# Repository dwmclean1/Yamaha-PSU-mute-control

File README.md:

# Yamaha-PSU-mute-control

## What is it?

<p>Allows the use of non-original power supplies in older Yamaha rackmount audio devices.</p><br>

<br>

<p/>The board consists of the bridge rectifier, 3 100K resistor and phototransistor shown above. When the unit is powered on this circuit provides current to the mute control ciruit on the main board which will activate the mute relays after a short delay in order to avoid any loud spikes from the audio outputs.</p><br>

<br>

<p>Most Yamaha audio gear from this era used the same power supply board, or at least the same circuit, and if you want to replace the power supply with a newer version you may need this circuit. Use at your own risk.</p><br>

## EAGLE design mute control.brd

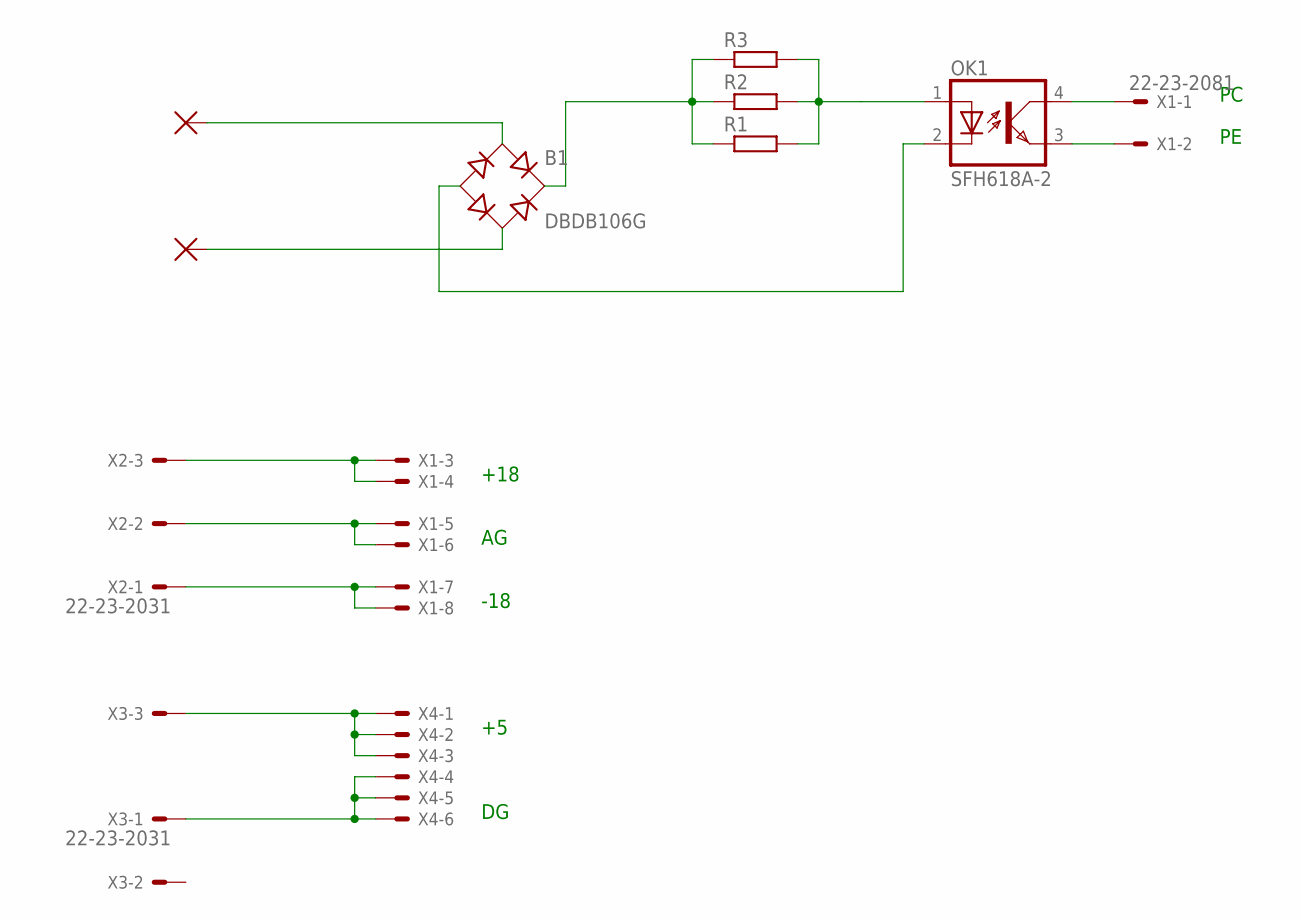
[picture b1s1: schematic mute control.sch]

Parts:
AC: 3,17/1,3; OBLONG
B1: DBDB106G; DB
OK1: SFH618A-2; DIP4
PAD1: 3,17/1,3; OBLONG
R1, R2, R3: R-EU_0817/22; P0817/22
X1: 22-23-2081
X2, X3: 22-23-2031
X4: 22-23-2061

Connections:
unnamed: AC.P$1, B1.AC2
unnamed: B1.AC1, PAD1.P$1
unnamed: B1.+, R1.1, R2.1, R3.1
unnamed: B1.-, OK1.2 (C)
unnamed: OK1.4 (COL), X1.1
unnamed: OK1.3 (EMIT), X1.2
unnamed: X1.3, X1.4, X2.3
unnamed: OK1.1 (A), R1.2, R2.2, R3.2
unnamed: X3.1, X4.4, X4.5, X4.6
unnamed: X3.3, X4.1, X4.2, X4.3
unnamed: X1.5, X1.6, X2.2
unnamed: X1.7, X1.8, X2.1

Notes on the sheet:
+18
-18

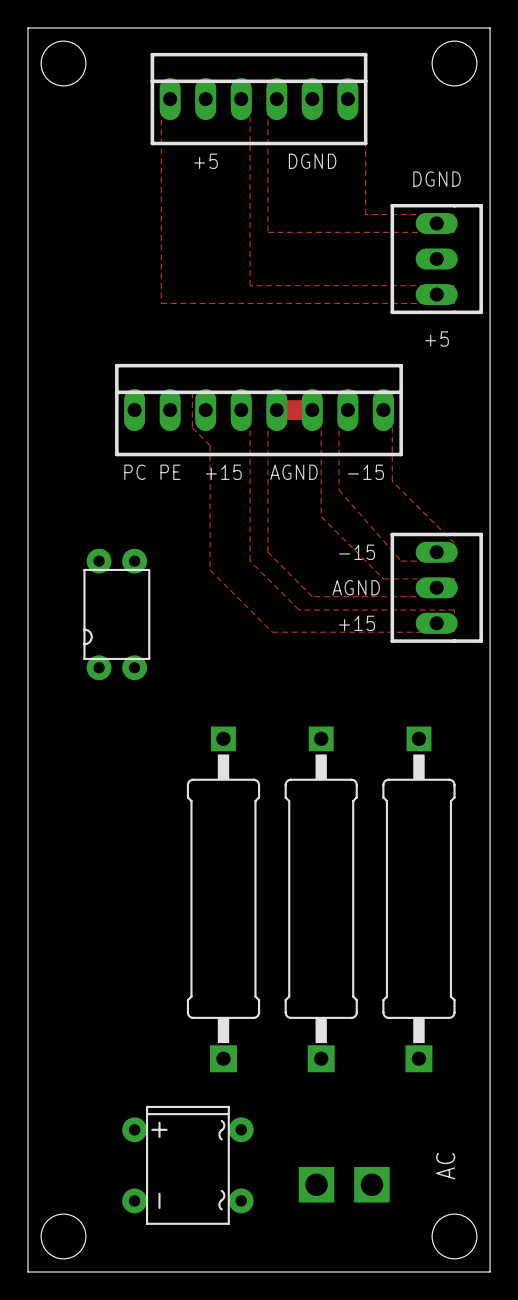
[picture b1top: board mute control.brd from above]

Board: 2 copper layers, 33.0 x 88.9 mm, 11 parts (0 on the bottom side), 12 nets.
